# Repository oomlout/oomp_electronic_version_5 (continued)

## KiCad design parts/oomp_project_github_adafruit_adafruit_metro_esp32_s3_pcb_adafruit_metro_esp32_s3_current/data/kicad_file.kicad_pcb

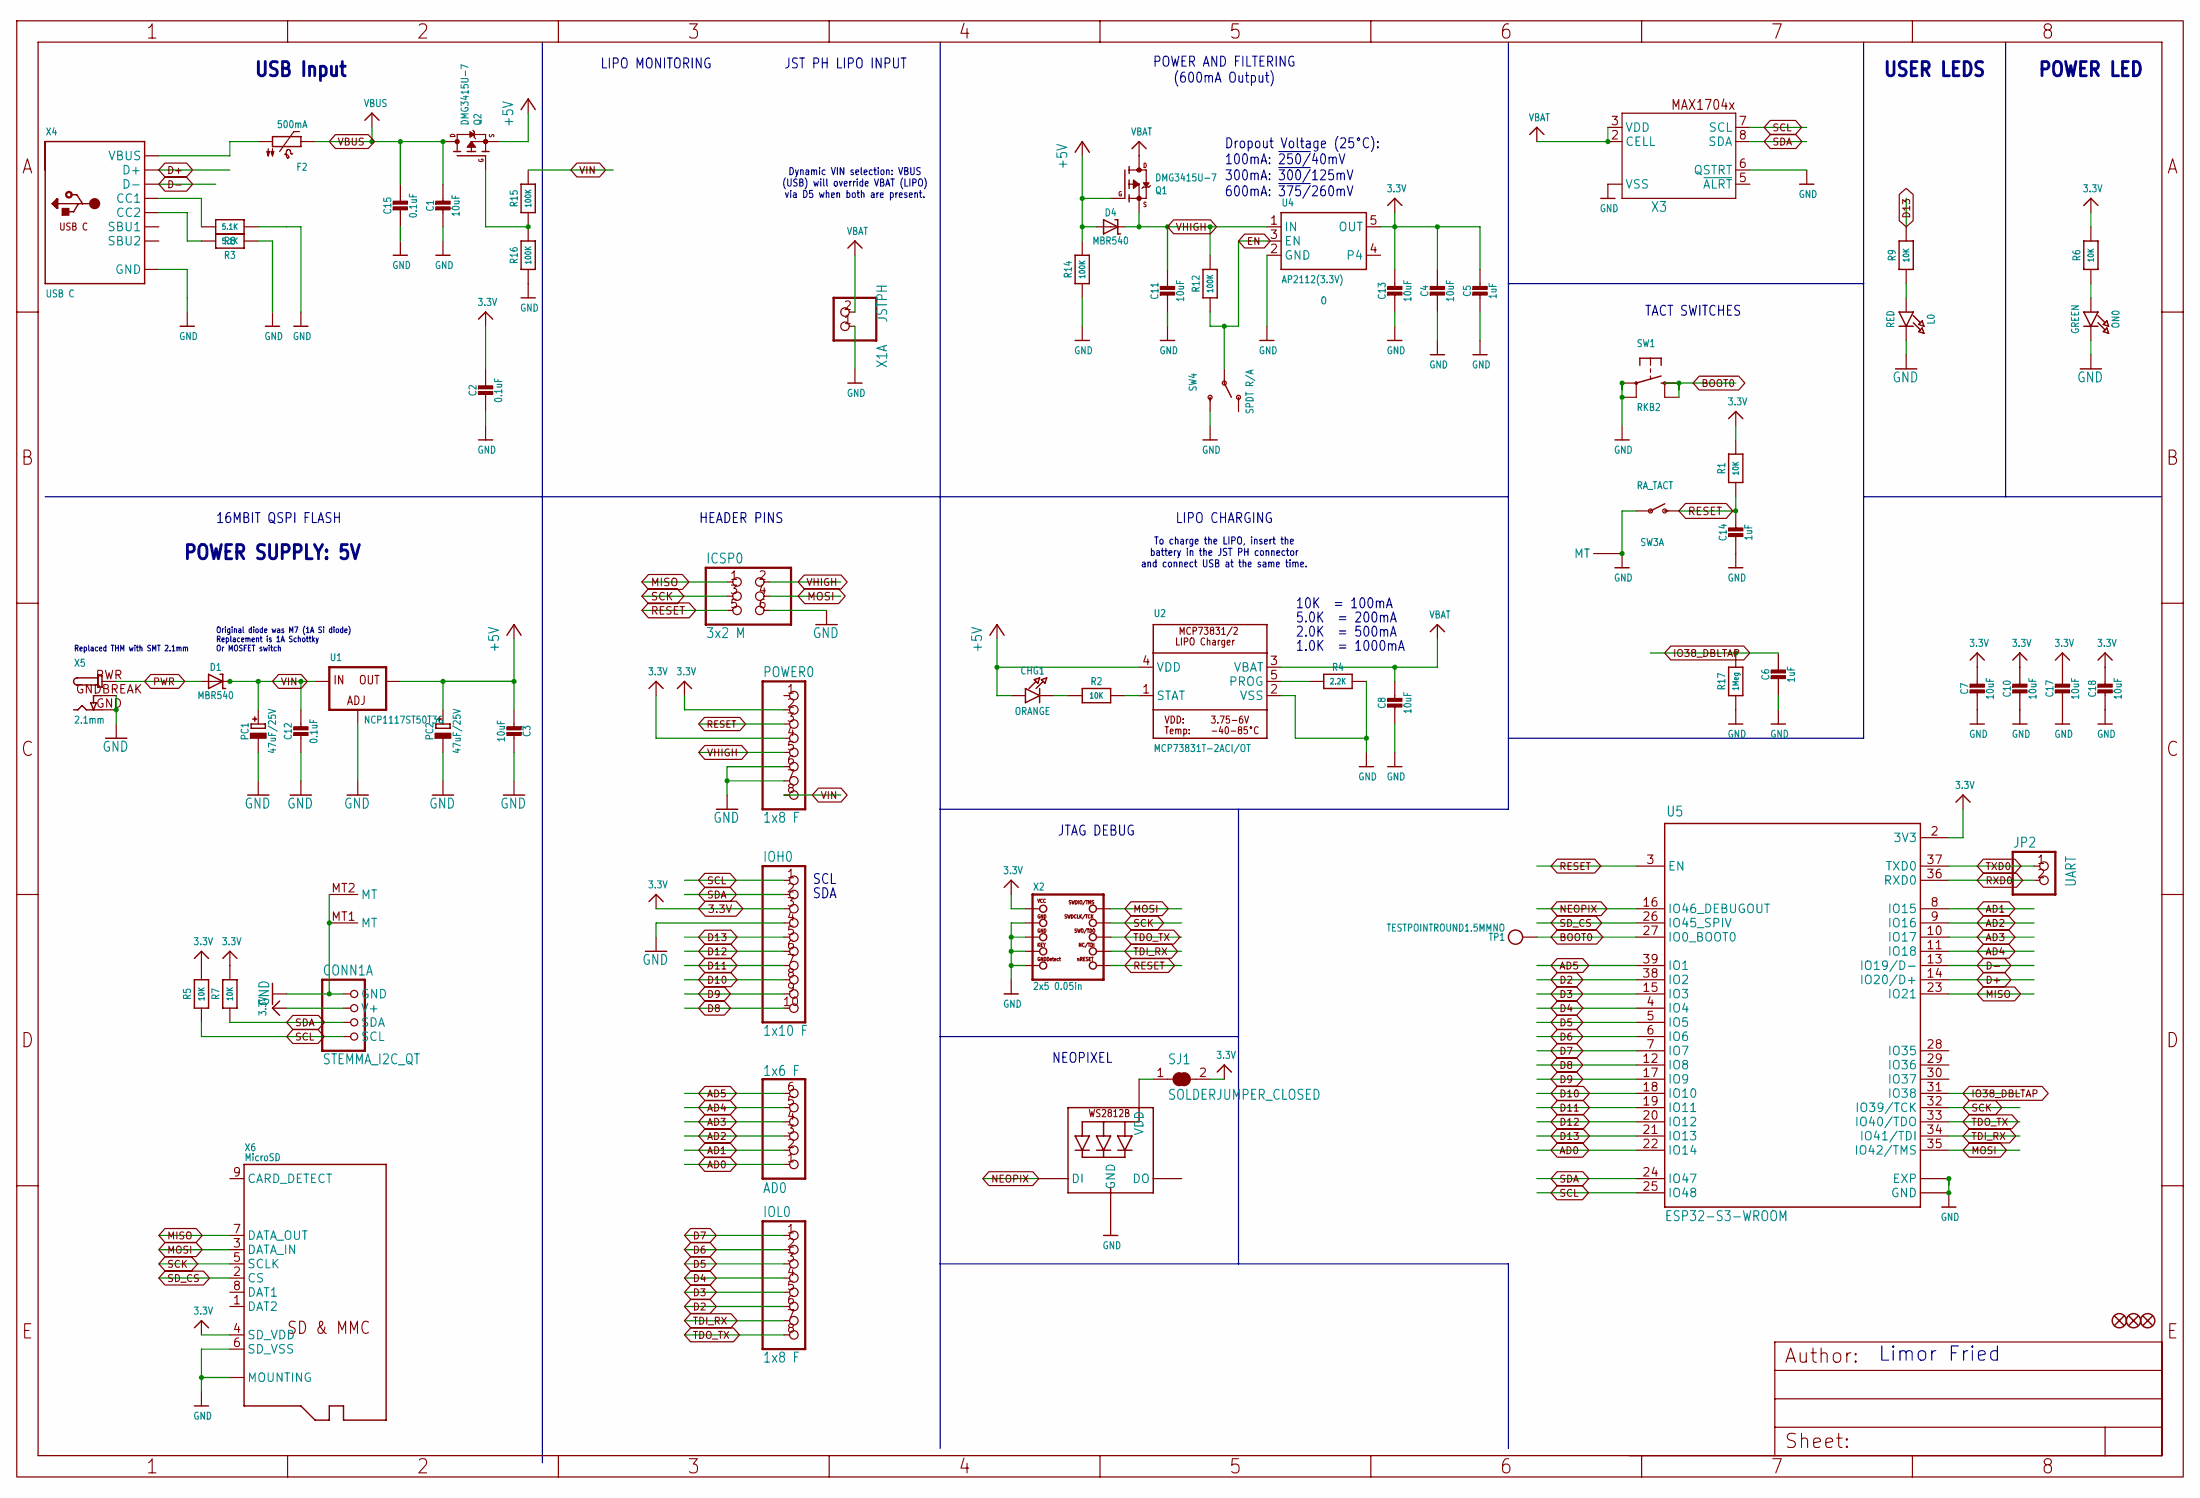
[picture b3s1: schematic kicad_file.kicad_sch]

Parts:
AD0: 1x6 F; 1X06_OVALWAVE
C1, C3, C4, C7, C8, C10, C11, C13, C17, C18: 10uF; 0805-NO
C2, C12, C15: 0.1uF; 0603-NO
C5, C6, C14: 1uF; 0603-NO
CHG1: ORANGE; CHIPLED_0603_NOOUTLINE
CONN1: STEMMA_I2C_QT; JST_SH4; LCSC C2845363
D1, D4: MBR540; SOD-123
F2: 500mA; 0805-NO
FD1, FD2, FD3: FIDUCIAL_1MM
ICSP0: 3x2 M; 2X03_ROUND_70MIL
IOH0: 1x10 F; 1X10_OVALWAVE
IOL0: 1x8 F; 1X08_OVALWAVE
JP2: UART; 1X02_ROUND
L0: RED; CHIPLED_0603_NOOUTLINE
LED1: WS2812B_3535FULL; LED3535_FULLPADS
ON0: GREEN; CHIPLED_0603_NOOUTLINE
PC1, PC2: 47uF/25V; PANASONIC_D
POWER0: 1x8 F; 1X08_OVALWAVE
Q1, Q2: DMG3415U-7; SOT23-R
R1, R2, R5, R6, R7, R9: 10K; 0603-NO
R3, R8: 5.1K; 0603-NO
R4: 2.2K; 0603-NO
R12, R14, R15, R16: 100K; 0603-NO
R17: 1Meg; 0603-NO
SJ1: SOLDERJUMPER_CLOSED; SOLDERJUMPER_CLOSEDWIRE
SW1: RKB2; BTN_RKB2_4.6X2.8
SW3: RA_TACT; SPST_TACTILE_RA; LCSC C778159
SW4: SPDT R/A; SPDT_SMT_SSSS811101
TP1: TESTPOINTROUND1.5MMNO; TESTPOINT_ROUND_1.5MM_NO
U1: NCP1117ST50T3G; SOT223-R
U2: MCP73831T-2ACI/OT; SOT23-5; JLC_ROTATION 0
U4: AP2112(3.3V); SOT23-5; JLC_ROTATION 0
U5: ESP32-S3-WROOM; S3-WROOM32
X1: JSTPH; JSTPH2_BATT; LCSC C47647
X2: 2x5 0.05in; 2X05_1.27MM_BOX_POSTS
X3: MAX17048/T; TDFN8_2X2MM
X4: USB C; USB_C_CUSB31-CFM2AX-01-X; LCSC C165948
X5: 2.1mm; DCJACK_2MM_PTH
X6: MicroSD; MOLEX_104031-0811

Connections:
3.3V: C2.1, C4.1, C5.1, C7.1, C10.1, C13.1, C17.1, C18.1, CONN1.2 (V+), IOH0.3, POWER0.2, POWER0.4, R1.2, R5.2, R6.2, R7.2, SJ1.2, U4.5 (OUT), U5.2 (3V3), X2.1 (VCC), X6.4 (SD_VDD)
+5V: C3.2, CHG1.A, D4.A, PC2.+, Q1.1 (G), Q2.2 (S), R14.2, U1.2 (OUT), U1.4 (OUT), U2.4 (VDD)
AD0: AD0.1, U5.22 (IO14)
AD1: AD0.2, U5.8 (IO15)
AD2: AD0.3, U5.9 (IO16)
AD3: AD0.4, U5.10 (IO17)
AD4: AD0.5, U5.11 (IO18)
AD5: AD0.6, U5.39 (IO1)
BOOT0: SW1.B (S), SW1.B' (S1), TP1.P$1, U5.27 (IO0_BOOT0)
D2: IOL0.6, U5.38 (IO2)
D3: IOL0.5, U5.15 (IO3)
D4: IOL0.4, U5.4 (IO4)
D5: IOL0.3, U5.5 (IO5)
D6: IOL0.2, U5.6 (IO6)
D7: IOL0.1, U5.7 (IO7)
D8: IOH0.10, U5.12 (IO8)
D9: IOH0.9, U5.17 (IO9)
D10: IOH0.8, U5.18 (IO10)
D11: IOH0.7, U5.19 (IO11)
D12: IOH0.6, U5.20 (IO12)
D13: IOH0.5, R9.2, U5.21 (IO13)
D+: U5.14 (IO20/D+), X4.A6 (D+), X4.B6 (D+)
D-: U5.13 (IO19/D-), X4.A7 (D-), X4.B7 (D-)
EN: R12.1, SW4.B, U4.3 (EN)
GND: C1.2, C2.2, C3.1, C4.2, C5.2, C6.2, C7.2, C8.2, C10.2, C11.2, C12.2, C13.2, C14.2, C15.2, C17.2, C18.2, CONN1.1 (GND), CONN1.MT1 (MT), CONN1.MT2 (MT), ICSP0.6, IOH0.4, L0.C, LED1.4 (GND), ON0.C, PC1.-, PC2.-, POWER0.6, POWER0.7, R3.1, R4.2, R8.1, R14.1, R16.1, R17.1, SW1.A, SW1.A' (P1), SW3.1, SW3.MT1 (MT), SW3.MT2 (MT), SW4.C (S), U1.1 (ADJ), U2.2 (VSS), U4.2 (GND), U5.1 (GND), U5.40 (GND), U5.P$2 (EXP), U5.P$3 (EXP), U5.P$4 (EXP), U5.P$5 (EXP), U5.P$6 (EXP), U5.P$7 (EXP), U5.P$8 (EXP), U5.P$9 (EXP), U5.P$10 (EXP), X1.1, X2.3 (GND), X2.5 (GND), X2.7 (KEY), X2.9 (GNDDETECT), X3.1 (VSS), X3.4 (VSS), X3.6 (QSTRT), X3.THERMAL (VSS), X4.A1B12 (GND), X4.B1A12 (GND), X5.GND, X5.GNDBREAK, X6.6 (SD_VSS), X6.10 (MOUNTING), X6.G1 (MOUNTING), X6.G2 (MOUNTING), X6.G3 (MOUNTING), X6.G4 (MOUNTING)
IO38_DBLTAP: C6.1, R17.2, U5.31 (IO38)
MISO: ICSP0.1, U5.23 (IO21), X6.7 (DATA_OUT)
MOSI: ICSP0.4, U5.35 (IO42/TMS), X2.2 (SWDIO), X6.3 (DATA_IN)
unnamed: L0.A, R9.1
unnamed: Q2.1 (G), R15.1, R16.2
unnamed: ON0.A, R6.1
unnamed: CHG1.C, R2.1
unnamed: LED1.2 (VDD), SJ1.1
unnamed: R2.2, U2.1 (STAT)
unnamed: R8.2, X4.A5 (CC1)
unnamed: R3.2, X4.B5 (CC2)
unnamed: R4.1, U2.5 (PROG)
unnamed: F2.1, X4.A4B9 (VBUS), X4.B4A9 (VBUS)
NEOPIX: LED1.1 (DI), U5.16 (IO46_DEBUGOUT)
PWR: D1.A, X5.PWR
RESET: C14.1, ICSP0.5, POWER0.3, R1.1, SW3.2 (S), U5.3 (EN), X2.10 (NRESET)
RXD0: JP2.2, U5.36 (RXD0)
SCK: ICSP0.3, U5.32 (IO39/TCK), X2.4 (SWDCLK), X6.5 (SCLK)
SCL: CONN1.4 (SCL), IOH0.1, R5.1, U5.25 (IO48), X3.7 (SCL)
SDA: CONN1.3 (SDA), IOH0.2, R7.1, U5.24 (IO47), X3.8 (SDA)
SD_CS: U5.26 (IO45_SPIV), X6.2 (CS)
TDI_RX: IOL0.7, U5.34 (IO41/TDI), X2.8 (TDI)
TDO_TX: IOL0.8, U5.33 (IO40/TDO), X2.6 (SWO)
TXD0: JP2.1, U5.37 (TXD0)
VBAT: C8.1, Q1.3 (D), U2.3 (VBAT), X1.2, X3.2 (CELL), X3.3 (VDD)
VBUS: C1.1, C15.1, F2.2, Q2.3 (D)
VHIGH: C11.1, D4.C, ICSP0.2, POWER0.5, Q1.2 (S), R12.2, U4.1 (IN)
VIN: C12.1, D1.C, PC1.+, POWER0.8, R15.2, U1.3 (IN)

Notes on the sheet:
HEADER PINS
2.0K = 500mA
USER LEDS
USB Input
JTAG DEBUG
POWER AND FILTERING (600mA Output)
5.0K = 200mA
SCL
JST PH LIPO INPUT
Replaced THM with SMT 2.1mm
Dynamic VIN selection: VBUS (USB) will override VBAT (LIPO) via D5 when both are present.
SDA
1.0K = 1000mA
Original diode was M7 (1A Si diode) Replacement is 1A Schottky Or MOSFET switch
10K = 100mA
TACT SWITCHES
LIPO CHARGING
Dropout Voltage (25°C): 100mA: ~{250/}40mV 300mA: ~{300/}125mV 600mA: ~{375/}260mV
16MBIT QSPI FLASH
POWER SUPPLY: 5V
To charge the LIPO, insert the battery in the JST PH connector and connect USB at the same time.
POWER LED
Limor Fried
LIPO MONITORING
NEOPIXEL

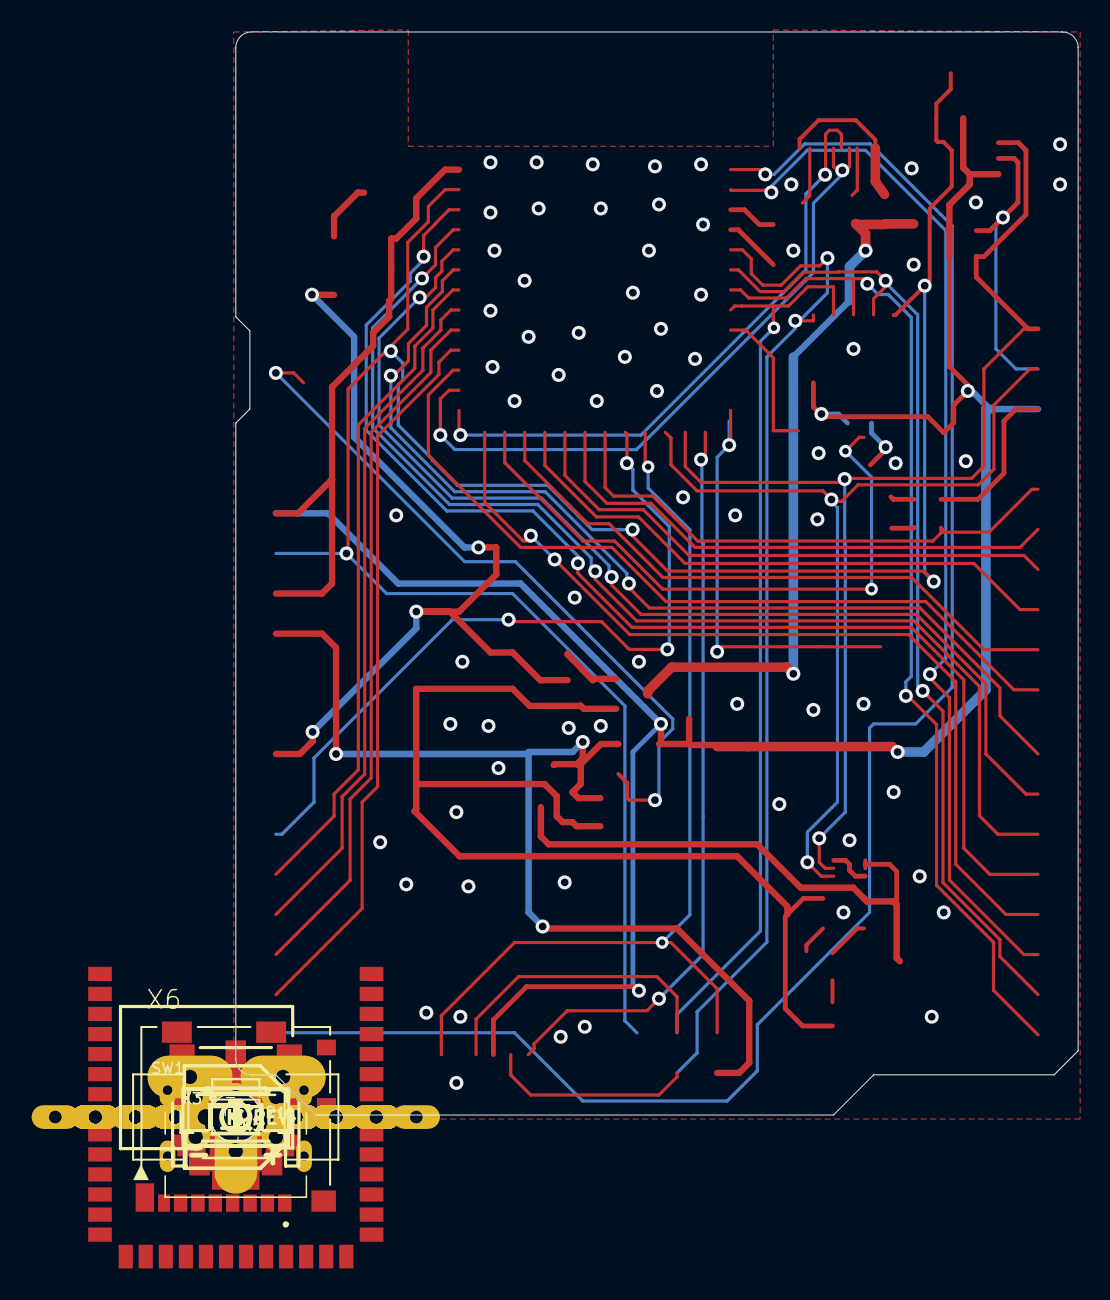
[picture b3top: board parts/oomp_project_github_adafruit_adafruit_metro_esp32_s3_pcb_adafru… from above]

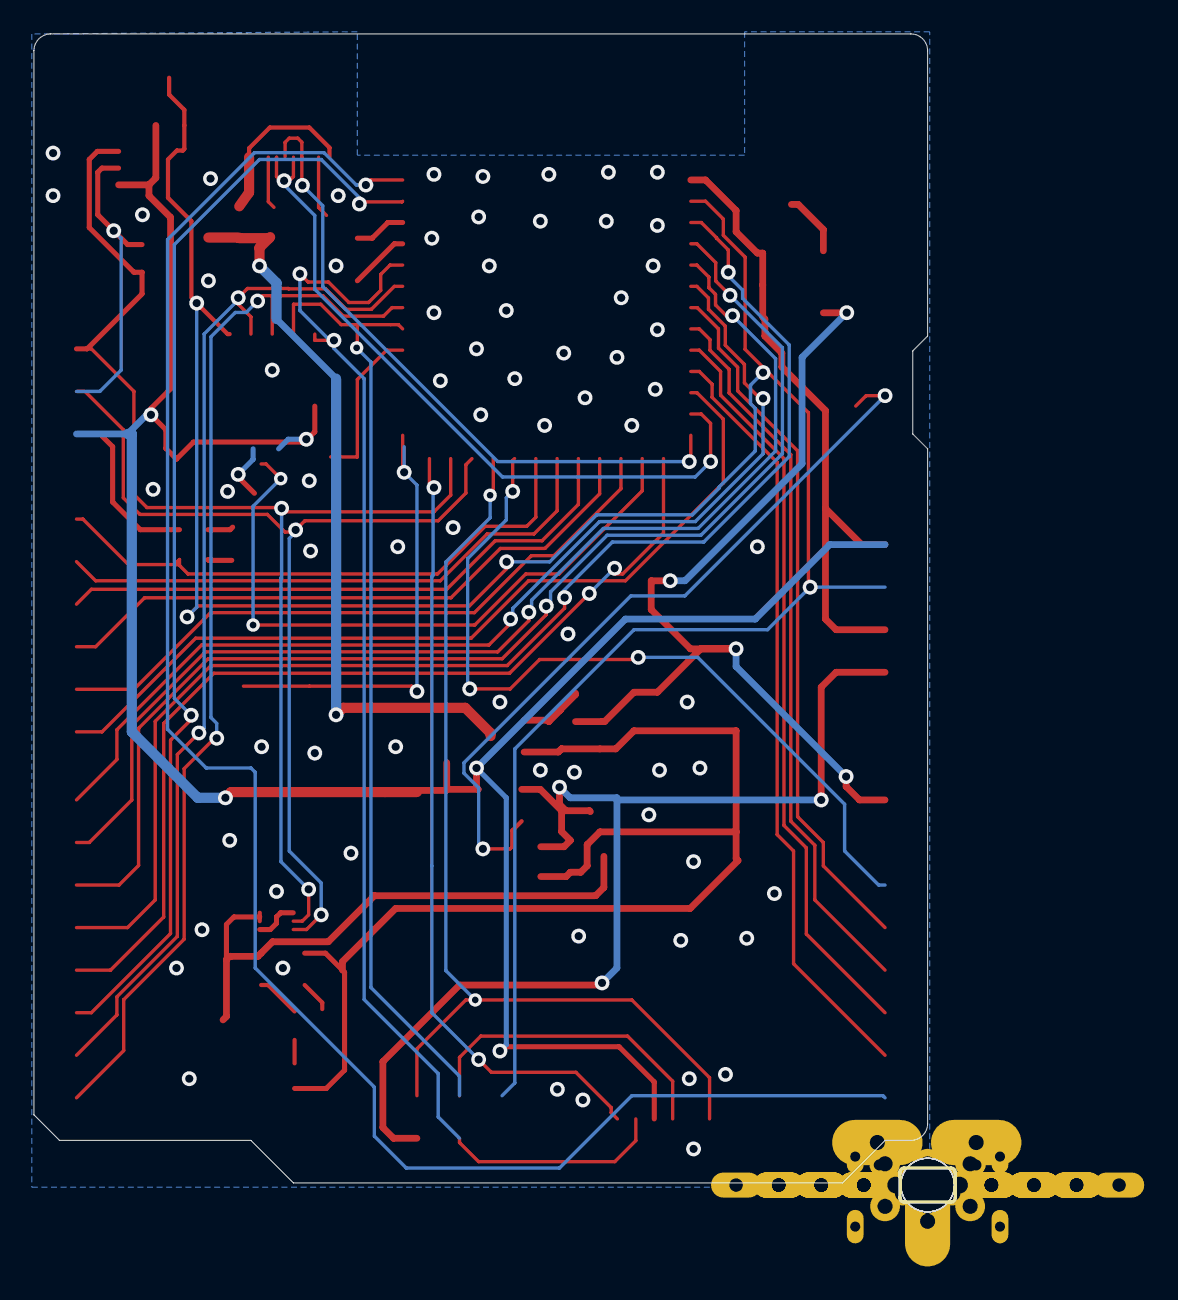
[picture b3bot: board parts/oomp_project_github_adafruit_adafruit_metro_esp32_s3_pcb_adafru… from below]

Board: 2 copper layers, 53.3 x 68.6 mm, 73 parts (3 on the bottom side), 53 nets.

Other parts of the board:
U$15: PCBFEAT-REV-040
U$52: METROS3_TOP
U$58: METROS3_BOT
UNK_HOLE_0: dummyfp0
UNK_HOLE_1: dummyfp1
UNK_HOLE_2: dummyfp2
UNK_HOLE_3: dummyfp3

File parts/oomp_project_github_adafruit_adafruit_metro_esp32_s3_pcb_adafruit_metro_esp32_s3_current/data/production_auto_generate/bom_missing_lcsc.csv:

Designator,Comment,Footprint,OOMP ID,Reason
C1,10uF,Adafruit Metro ESP32-S3 Rev B-import-fps:0805-NO,electronic_capacitor_0805_10_micro_farad,No verified LCSC part number
C3,10uF,Adafruit Metro ESP32-S3 Rev B-import-fps:0805-NO,electronic_capacitor_0805_10_micro_farad,No verified LCSC part number
C4,10uF,Adafruit Metro ESP32-S3 Rev B-import-fps:0805-NO,electronic_capacitor_0805_10_micro_farad,No verified LCSC part number
C7,10uF,Adafruit Metro ESP32-S3 Rev B-import-fps:0805-NO,electronic_capacitor_0805_10_micro_farad,No verified LCSC part number
C8,10uF,Adafruit Metro ESP32-S3 Rev B-import-fps:0805-NO,electronic_capacitor_0805_10_micro_farad,No verified LCSC part number
C10,10uF,Adafruit Metro ESP32-S3 Rev B-import-fps:0805-NO,electronic_capacitor_0805_10_micro_farad,No verified LCSC part number
C11,10uF,Adafruit Metro ESP32-S3 Rev B-import-fps:0805-NO,electronic_capacitor_0805_10_micro_farad,No verified LCSC part number
C13,10uF,Adafruit Metro ESP32-S3 Rev B-import-fps:0805-NO,electronic_capacitor_0805_10_micro_farad,No verified LCSC part number
C17,10uF,Adafruit Metro ESP32-S3 Rev B-import-fps:0805-NO,electronic_capacitor_0805_10_micro_farad,No verified LCSC part number
C18,10uF,Adafruit Metro ESP32-S3 Rev B-import-fps:0805-NO,electronic_capacitor_0805_10_micro_farad,No verified LCSC part number
CHG1,ORANGE,Adafruit Metro ESP32-S3 Rev B-import-fps:CHIPLED_0603_NOOUTLINE,electronic_led_0603,No verified LCSC part number
D1,MBR540,Adafruit Metro ESP32-S3 Rev B-import-fps:SOD-123,,No verified LCSC part number
D4,MBR540,Adafruit Metro ESP32-S3 Rev B-import-fps:SOD-123,,No verified LCSC part number
F2,500mA,Adafruit Metro ESP32-S3 Rev B-import-fps:0805-NO,,No verified LCSC part number
FD1,FIDUCIAL_1MM,Adafruit Metro ESP32-S3 Rev B-import-fps:FIDUCIAL_1MM,,No verified LCSC part number
FD2,FIDUCIAL_1MM,Adafruit Metro ESP32-S3 Rev B-import-fps:FIDUCIAL_1MM,,No verified LCSC part number
FD3,FIDUCIAL_1MM,Adafruit Metro ESP32-S3 Rev B-import-fps:FIDUCIAL_1MM,,No verified LCSC part number
ICSP0,3x2 M,Adafruit Metro ESP32-S3 Rev B-import-fps:2X03_ROUND_70MIL,,No verified LCSC part number
L0,RED,Adafruit Metro ESP32-S3 Rev B-import-fps:CHIPLED_0603_NOOUTLINE,electronic_led_0603_red,No verified LCSC part number
LED1,WS2812B_3535FULL,Adafruit Metro ESP32-S3 Rev B-import-fps:LED3535_FULLPADS,,No verified LCSC part number
ON0,GREEN,Adafruit Metro ESP32-S3 Rev B-import-fps:CHIPLED_0603_NOOUTLINE,electronic_led_0603_green,No verified LCSC part number
PC1,47uF/25V,Adafruit Metro ESP32-S3 Rev B-import-fps:PANASONIC_D,,No verified LCSC part number
PC2,47uF/25V,Adafruit Metro ESP32-S3 Rev B-import-fps:PANASONIC_D,,No verified LCSC part number
Q1,DMG3415U-7,Adafruit Metro ESP32-S3 Rev B-import-fps:SOT23-R,,No verified LCSC part number
Q2,DMG3415U-7,Adafruit Metro ESP32-S3 Rev B-import-fps:SOT23-R,,No verified LCSC part number
SW1,RKB2,Adafruit Metro ESP32-S3 Rev B-import-fps:BTN_RKB2_4.6X2.8,,No verified LCSC part number
SW3,RA_TACT,Adafruit Metro ESP32-S3 Rev B-import-fps:SPST_TACTILE_RA,,No verified LCSC part number
SW4,SPDT R/A,Adafruit Metro ESP32-S3 Rev B-import-fps:SPDT_SMT_SSSS811101,,No verified LCSC part number
TP1,,Adafruit Metro ESP32-S3 Rev B-import-fps:TESTPOINT_ROUND_1.5MM_NO,,No verified LCSC part number
U1,NCP1117ST50T3G,Adafruit Metro ESP32-S3 Rev B-import-fps:SOT223-R,,No verified LCSC part number
U2,MCP73831T-2ACI/OT,Adafruit Metro ESP32-S3 Rev B-import-fps:SOT23-5,,No verified LCSC part number
U4,AP2112(3.3V),Adafruit Metro ESP32-S3 Rev B-import-fps:SOT23-5,,No verified LCSC part number
U5,ESP32-S3-WROOM,Adafruit Metro ESP32-S3 Rev B-import-fps:S3-WROOM32,,No verified LCSC part number
U$15,,Adafruit Metro ESP32-S3 Rev B-import-fps:PCBFEAT-REV-040,,No verified LCSC part number
U$52,,Adafruit Metro ESP32-S3 Rev B-import-fps:METROS3_TOP,,No verified LCSC part number
U$58,,Adafruit Metro ESP32-S3 Rev B-import-fps:METROS3_BOT,,No verified LCSC part number
X1,JSTPH,Adafruit Metro ESP32-S3 Rev B-import-fps:JSTPH2_BATT,,No verified LCSC part number
X2,2x5 0.05in,Adafruit Metro ESP32-S3 Rev B-import-fps:2X05_1.27MM_BOX_POSTS,,No verified LCSC part number
X3,MAX17048/T,Adafruit Metro ESP32-S3 Rev B-import-fps:TDFN8_2X2MM,,No verified LCSC part number
X4,USB C,Adafruit Metro ESP32-S3 Rev B-import-fps:USB_C_CUSB31-CFM2AX-01-X,,No verified LCSC part number
X5,2.1mm,Adafruit Metro ESP32-S3 Rev B-import-fps:DCJACK_2MM_PTH,,No verified LCSC part number
X6,MicroSD,Adafruit Metro ESP32-S3 Rev B-import-fps:MOLEX_104031-0811,,No verified LCSC part number

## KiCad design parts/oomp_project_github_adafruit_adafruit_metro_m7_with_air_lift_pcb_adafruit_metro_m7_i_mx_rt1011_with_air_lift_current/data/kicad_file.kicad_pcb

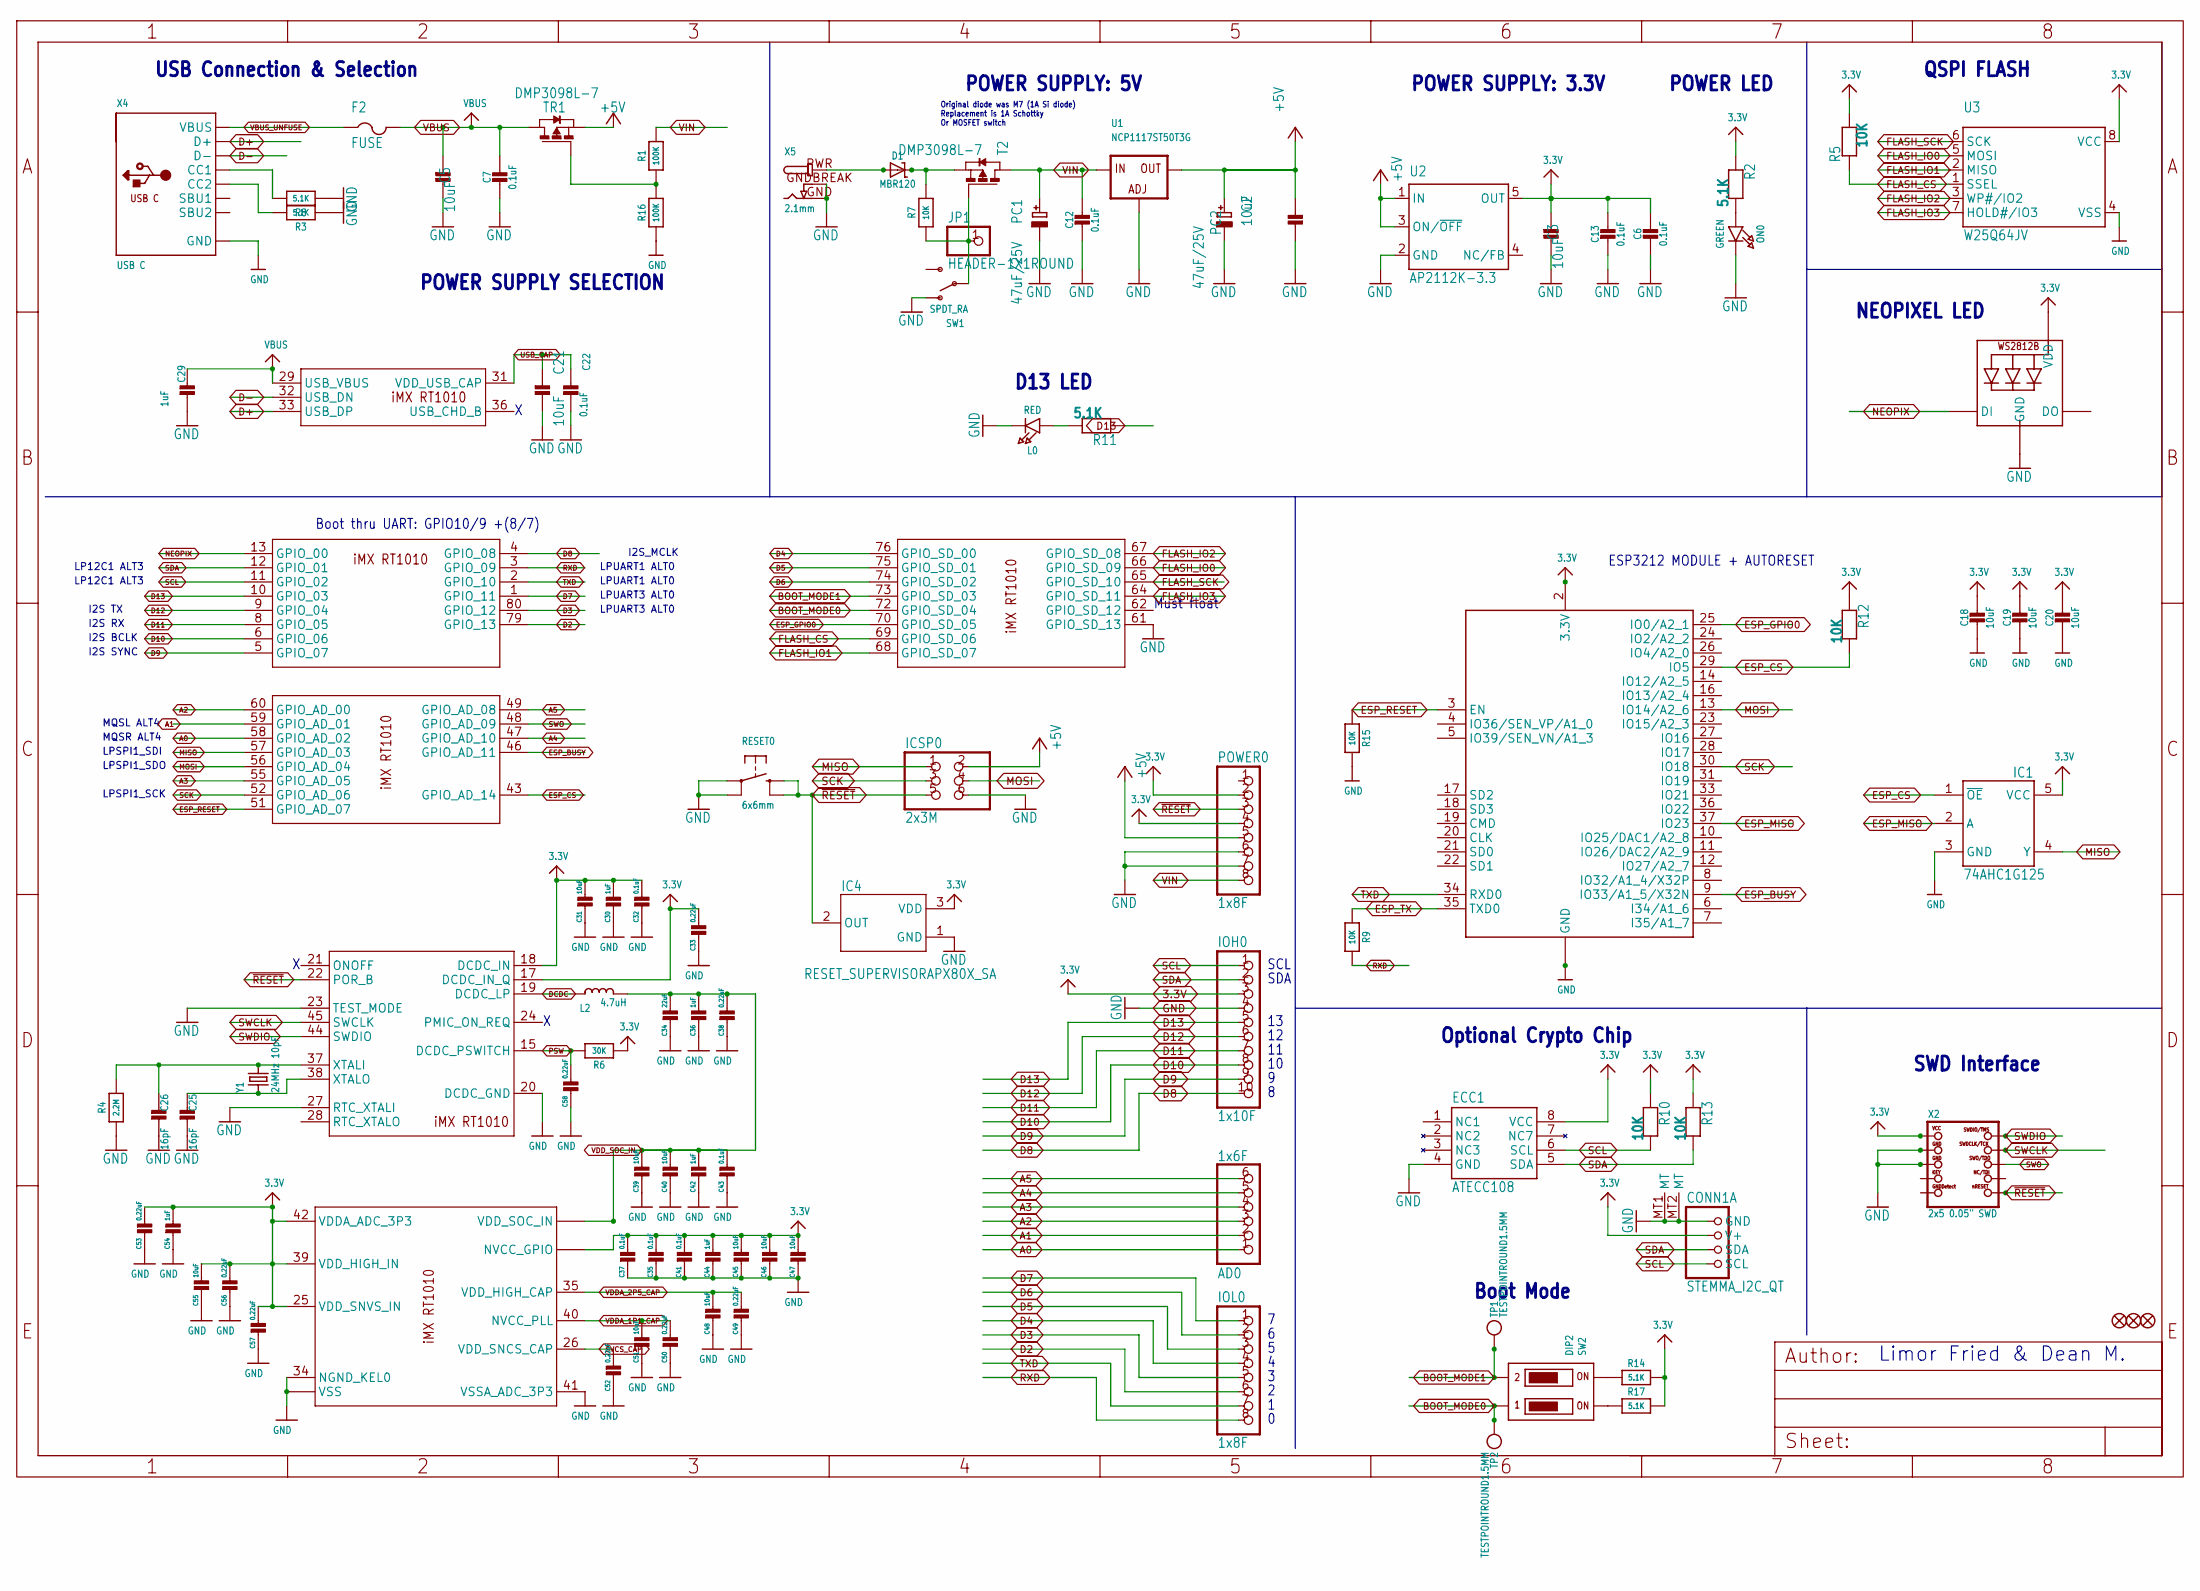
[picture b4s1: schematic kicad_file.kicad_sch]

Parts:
AD0: 1x6F; 1X06_OVALWAVE
C2, C3, C5, C18, C19, C20, C21, C31, C39, C40, C45, C46, C47, C48, C51, C55: 10uF; 0805-NO
C6, C7, C12, C13, C22, C32, C35, C37, C41, C43: 0.1uF; 0603-NO
C25, C26: 16pF; 0603-NO
C29, C30, C36, C42, C44, C54: 1uF; 0603-NO
C33, C38, C49, C50, C52, C53, C56, C57, C58: 0.22uF; 0603-NO
C34: 22uF; 0805-NO
CONN1: STEMMA_I2C_QT; JST_SH4; LCSC C2845363
D1: MBR120; SOD-123
ECC1: ATECC108; SOIC8
F2: FUSE; R1206
FD1, FD2, FD3: FIDUCIAL_1MM
IC1: 74AHC1G125; SOT23-5L
IC2: IMX_RT1010; QFP50P1400X1400X160-80N
IC4: RESET_SUPERVISORAPX80X_SA; SOT23-WIDE
ICSP0: 2x3M; 2X03_ROUND_70MIL
IOH0: 1x10F; 1X10_OVALWAVE
IOL0: 1x8F; 1X08_OVALWAVE
JP1: HEADER-1X1ROUND; 1X01_ROUND
L0: RED; CHIPLED_0603_NOOUTLINE
L2: 4.7uH; INDUCTOR_1007
LED1: WS2812B_3535FULL; LED3535_FULLPADS
ON0: GREEN; CHIPLED_0603_NOOUTLINE
PC1, PC2: 47uF/25V; PANASONIC_D
POWER0: 1x8F; 1X08_OVALWAVE
R1, R16: 100K; 0603-NO
R2, R3, R8, R11, R14, R17: 5.1K; 0603-NO
R4: 2.2M; 0603-NO
R5, R7, R9, R10, R12, R13, R15: 10K; 0603-NO
R6: 30K; 0603-NO
RESET0: 6x6mm; EVQ-Q2_SMALLER
SW1: SPDT_RA; SPDT_SMT_SSSS811101
SW2: DIP2; DIPSWITCH_2PIN
T2: DMP3098L-7; SOT-23
TP1, TP2: TESTPOINTROUND1.5MM; TESTPOINT_ROUND_1.5MM
TR1: DMP3098L-7; SOT-23; PART_NUMBER PMV48XP
U1: NCP1117ST50T3G; SOT223-R
U2: AP2112K-3.3; SOT23-DBV
U3: W25Q64JV; SOIC8_208MIL
X2: 2x5 0.05" SWD; 2X05_1.27MM_BOX_POSTS
X4: USB C; USB_C_CUSB31-CFM2AX-01-X; LCSC C165948
X5: 2.1mm; DCJACK_2MM_PTH
X6: ESP32_WROOM32; WROOM32
Y1: 24MHz 10pF; CRYSTAL_2.5X2

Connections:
3.3V: C3.2, C6.2, C13.1, C18.1, C19.1, C20.1, C30.1, C31.1, C32.1, C33.1, C35.1, C37.1, C41.1, C44.1, C45.1, C46.1, C47.1, C53.1, C54.1, C55.1, C56.1, C57.1, CONN1.2 (V+), ECC1.8 (VCC), IC1.5 (VCC), IC2.7 (NVCC_GPIO), IC2.17 (DCDC_IN_Q), IC2.18 (DCDC_IN), IC2.25 (VDD_SNVS_IN), IC2.39 (VDD_HIGH_IN), IC2.42 (VDDA_ADC_3P3), IC2.50 (NVCC_GPIO), IC2.63 (NVCC_GPIO), IC2.71 (NVCC_GPIO), IC4.3 (VDD), IOH0.3, LED1.2 (VDD), POWER0.2, POWER0.4, R2.1, R5.2, R6.1, R10.1, R12.1, R13.1, R14.2, R17.2, U2.5 (OUT), U3.8 (VCC), X2.1 (VCC), X6.2 (3.3V)
+5V: C2.2, ICSP0.2, PC2.+, POWER0.5, TR1.2 (S), U1.2 (OUT), U1.4 (OUT), U2.1 (IN), U2.3 (ON/~OFF)
A0: AD0.1, IC2.58 (GPIO_AD_02)
A1: AD0.2, IC2.59 (GPIO_AD_01)
A2: AD0.3, IC2.60 (GPIO_AD_00)
A3: AD0.4, IC2.55 (GPIO_AD_05)
A4: AD0.5, IC2.47 (GPIO_AD_10)
A5: AD0.6, IC2.49 (GPIO_AD_08)
BOOT_MODE0: IC2.72 (GPIO_SD_04), SW2.1OFF, TP2.P$1
BOOT_MODE1: IC2.73 (GPIO_SD_03), SW2.2OFF, TP1.P$1
D2: IC2.79 (GPIO_13), IOL0.6
D3: IC2.80 (GPIO_12), IOL0.5
D4: IC2.76 (GPIO_SD_00), IOL0.4
D5: IC2.75 (GPIO_SD_01), IOL0.3
D6: IC2.74 (GPIO_SD_02), IOL0.2
D7: IC2.1 (GPIO_11), IOL0.1
D8: IC2.4 (GPIO_08), IOH0.10
D9: IC2.5 (GPIO_07), IOH0.9
D10: IC2.6 (GPIO_06), IOH0.8
D11: IC2.8 (GPIO_05), IOH0.7
D12: IC2.9 (GPIO_04), IOH0.6
D13: IC2.10 (GPIO_03), IOH0.5, R11.1
D+: IC2.33 (USB_DP), X4.A6 (D+), X4.B6 (D+)
D-: IC2.32 (USB_DN), X4.A7 (D-), X4.B7 (D-)
DCDC: IC2.19 (DCDC_LP), L2.P$1 (1)
ESP_BUSY: IC2.46 (GPIO_AD_11), X6.9 (IO33/A1_5/X32N)
ESP_CS: IC1.1 (~OE), IC2.43 (GPIO_AD_14), R12.2, X6.29 (IO5)
ESP_GPIO0: IC2.70 (GPIO_SD_05), X6.25 (IO0/A2_1)
ESP_MISO: IC1.2 (A), X6.37 (IO23)
ESP_RESET: IC2.51 (GPIO_AD_07), R15.1, X6.3 (EN)
ESP_TX: R9.1, X6.35 (TXD0)
FLASH_CS: IC2.69 (GPIO_SD_06), R5.1, U3.1 (SSEL)
FLASH_IO0: IC2.66 (GPIO_SD_09), U3.5 (MOSI)
FLASH_IO1: IC2.68 (GPIO_SD_07), U3.2 (MISO)
FLASH_IO2: IC2.67 (GPIO_SD_08), U3.3 (WP#/IO2)
FLASH_IO3: IC2.64 (GPIO_SD_11), U3.7 (HOLD#/IO3)
FLASH_SCK: IC2.65 (GPIO_SD_10), U3.6 (SCK)
GND: C2.1, C3.1, C5.1, C6.1, C7.2, C12.2, C13.2, C18.2, C19.2, C20.2, C21.1, C22.2, C25.2, C26.2, C29.2, C30.2, C31.2, C32.2, C33.2, C34.2, C35.2, C36.2, C37.2, C38.2, C39.2, C40.2, C41.2, C42.2, C43.2, C44.2, C45.2, C46.2, C47.2, C48.2, C49.2, C50.2, C51.2, C52.2, C53.2, C54.2, C55.2, C56.2, C57.2, C58.2, CONN1.1 (GND), CONN1.MT1 (MT), CONN1.MT2 (MT), ECC1.4 (GND), IC1.3 (GND), IC2.16 (VSS), IC2.20 (DCDC_GND), IC2.23 (TEST_MODE), IC2.27 (RTC_XTALI), IC2.30 (VSS), IC2.34 (NGND_KEL0), IC2.41 (VSSA_ADC_3P3), IC2.54 (VSS), IC2.61 (GPIO_SD_13), IC2.78 (VSS), IC4.1 (GND), ICSP0.6, IOH0.4, L0.C, LED1.4 (GND), ON0.C, PC1.-, PC2.-, POWER0.6, POWER0.7, R3.1, R4.1, R8.1, R15.2, R16.1, RESET0.A, RESET0.A' (P1), SW1.A (O), U1.1 (ADJ), U2.2 (GND), U3.4 (VSS), X2.3 (GND), X2.5 (GND), X4.A1B12 (GND), X4.B1A12 (GND), X5.GND, X5.GNDBREAK, X6.1 (GND), X6.15 (GND), X6.38 (GND), X6.P$1 (GND)
MISO: IC1.4 (Y), IC2.57 (GPIO_AD_03), ICSP0.1
MOSI: IC2.56 (GPIO_AD_04), ICSP0.4, X6.13 (IO14/A2_6)
unnamed: L0.A, R11.2
unnamed: ON0.A, R2.2
unnamed: R14.1, SW2.2ON
unnamed: R17.1, SW2.1ON
unnamed: R8.2, X4.A5 (CC1)
unnamed: R3.2, X4.B5 (CC2)
unnamed: C26.1, IC2.37 (XTALI), R4.2, Y1.3 (2)
unnamed: C25.1, IC2.38 (XTALO), Y1.1
unnamed: R1.1, R16.2, TR1.3 (G)
unnamed: D1.C, R7.2, T2.2 (S)
NEOPIX: IC2.13 (GPIO_00), LED1.1 (DI)
PSW: C58.1, IC2.15 (DCDC_PSWITCH), R6.2
PWRIN: D1.A, X5.PWR
PWR_SWITCH: JP1.1, R7.1, SW1.B, T2.3 (G)
RXD: IC2.3 (GPIO_09), IOL0.8, R9.2
SCK: IC2.52 (GPIO_AD_06), ICSP0.3, X6.30 (IO18)
SCL: CONN1.4 (SCL), ECC1.6 (SCL), IC2.11 (GPIO_02), IOH0.1, R10.2
SDA: CONN1.3 (SDA), ECC1.5 (SDA), IC2.12 (GPIO_01), IOH0.2, R13.2
SVCS_CAP: C52.1, IC2.26 (VDD_SNCS_CAP)
SWCLK: IC2.45 (SWCLK), X2.4 (SWDCLK)
SWDIO: IC2.44 (SWDIO), X2.2 (SWDIO)
SWO: IC2.48 (GPIO_AD_09), X2.6 (SWO)
TXD: IC2.2 (GPIO_10), IOL0.7, X6.34 (RXD0)
USB_CAP: C21.2, C22.1, IC2.31 (VDD_USB_CAP)
VBUS: C5.2, C7.1, C29.1, F2.2, IC2.29 (USB_VBUS), TR1.1 (D)
VBUS_UNFUSE: F2.1, X4.A4B9 (VBUS), X4.B4A9 (VBUS)
VDDA_1P1_CAP: C50.1, C51.1, IC2.40 (NVCC_PLL)
VDDA_2P5_CAP: C48.1, C49.1, IC2.35 (VDD_HIGH_CAP)
VDD_SOC_IN: C34.1, C36.1, C38.1, C39.1, C40.1, C42.1, C43.1, IC2.14 (VDD_SOC_IN), IC2.53 (VDD_SOC_IN), IC2.77 (VDD_SOC_IN), L2.P$2 (2)
VIN: C12.1, PC1.+, POWER0.8, R1.2, T2.1 (D), U1.3 (IN)
~RESET: IC2.22 (POR_B), IC4.2 (OUT), ICSP0.5, POWER0.3, RESET0.B (S), RESET0.B' (S1), X2.10 (NRESET)

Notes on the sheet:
Must float
MQSL ALT4
LPUART1 ALT0
NEOPIXEL LED
I2S SYNC
D13 LED
ESP3212 MODULE + AUTORESET
POWER SUPPLY: 5V
USB Connection & Selection
POWER LED
Boot thru UART: GPIO10/9 +(8/7)
LPUART3 ALT0
LPSPI1_SCK
QSPI FLASH
I2S_MCLK
LP12C1 ALT3
I2S TX
LPSPI1_SDO
Optional Crypto Chip
POWER SUPPLY SELECTION
Limor Fried & Dean M.
Original diode was M7 (1A Si diode) Replacement is 1A Schottky Or MOSFET switch
Boot Mode
I2S BCLK
LPSPI1_SDI
POWER SUPPLY: 3.3V
SCL
I2S RX
SWD Interface
MQSR ALT4
SDA
